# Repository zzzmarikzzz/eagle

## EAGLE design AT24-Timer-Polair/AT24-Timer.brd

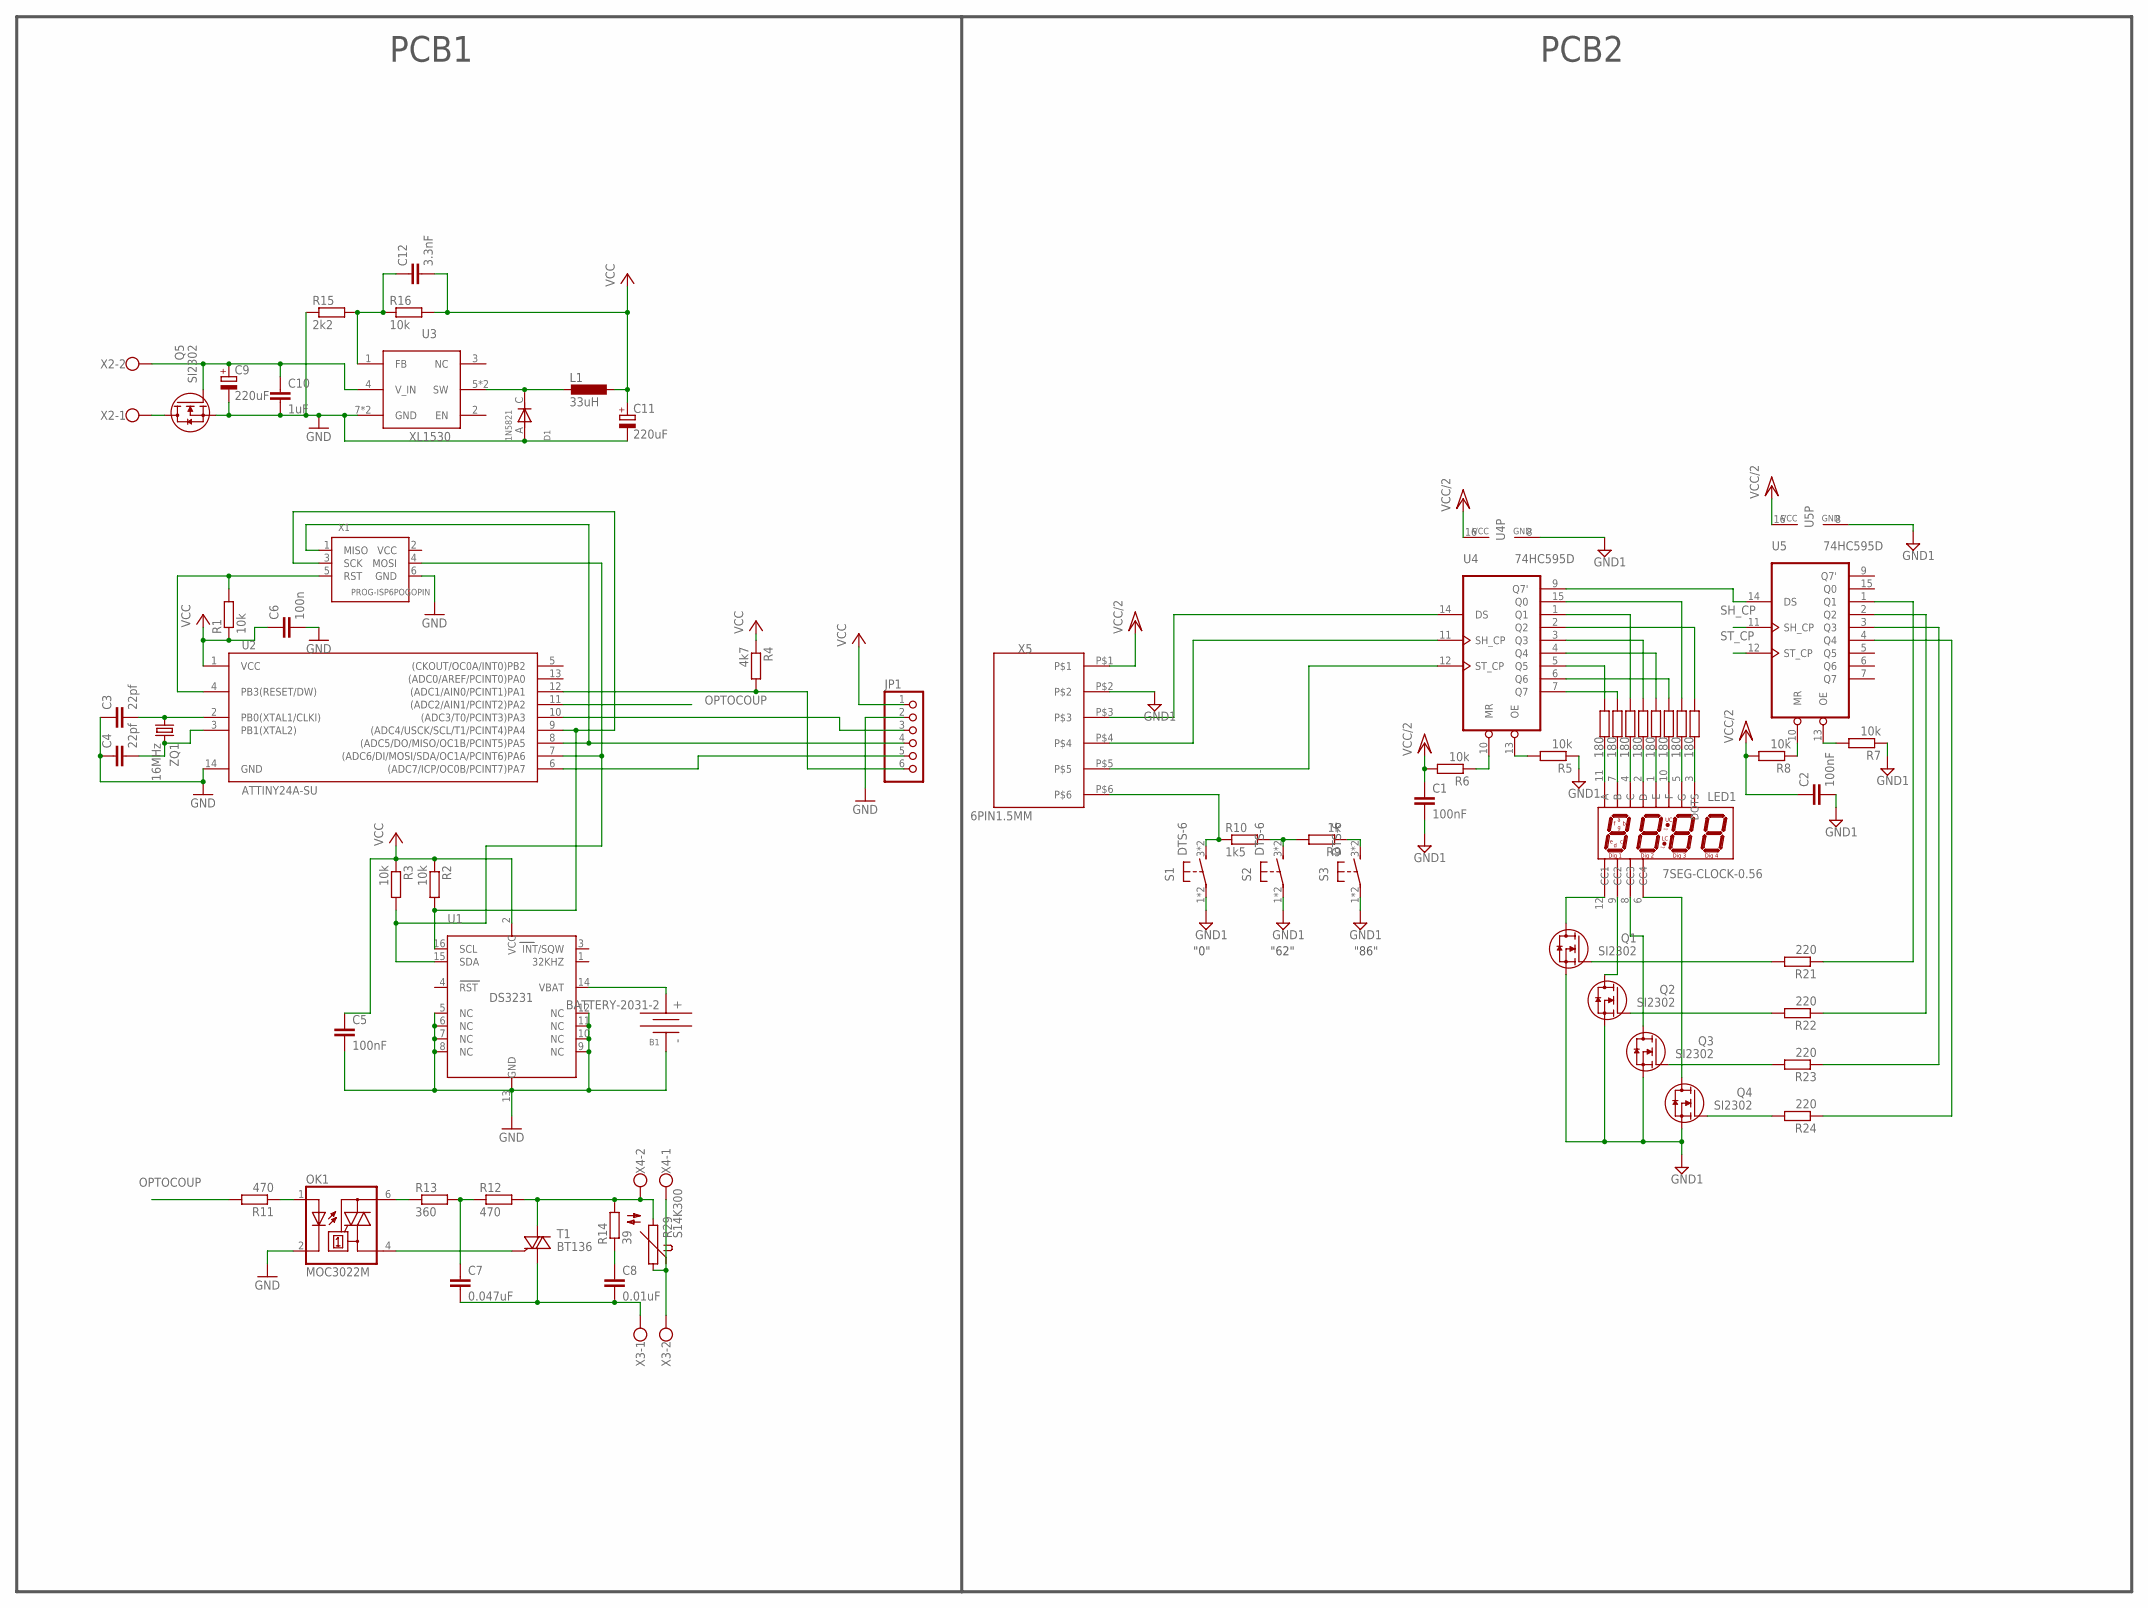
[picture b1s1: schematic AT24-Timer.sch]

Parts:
B1: BATTERY-2031-2; BTH2032-2
C1, C2, C5: 100nF; C0603
C3, C4: 22pf; C0603
C6: 100n; C0603
C7: 0.047uF; C150-054X183
C8: 0.01uF; C102-043X133
C9, C11: 220uF; E2,5-6E
C10: 1uF; C0805
C12: 3.3nF; C0805
D1: 1N5821; DO214AC
JP1: PINHD-1X6; 1X06
L1: 33uH; L-SMD-D10
LED1: 7SEG-CLOCK-0.56; 7SEG_4DIG_0.56
OK1: MOC3022M; DIL06
Q1, Q2, Q3, Q4, Q5: SI2302; SOT-23-GSD
R1, R2, R3, R5, R6, R7, R8: 10k; R0805
R4: 4k7; R0805
R9: 1k; R0805
R10: 1k5; R0805
R11: 470; R0805
R12: 470; 0207/7
R13: 360; 0207/7
R14: 39; 0207/7
R15: 2k2; R0603
R16: 10k; R0603
R17, R18, R19, R20, R25, R26, R27, R28: 180; R0805
R21, R22, R23, R24: 220; R0805
R29: S14K300
S1, S2, S3: DTS-6
T1: BT136; TO220AB
U1: DS3231; SO16L
U2: ATTINY24A-SU; SO14
U3: XL1530; SOP08
U4, U5: 74HC595D; SO16
X1: PROG-ISP6POGOPIN; PROG_POGOPIN
X2, X3, X4: W237-102
X5: 6PIN1.5MM; 6PIN*1.5MM
ZQ1: 16MHz; HC49/S

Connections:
GND: B1.-, C3.1, C4.1, C5.2, C6.2, C9.-, C10.2, C11.-, D1.A (ANOD), JP1.2, OK1.2 (C), Q5.S, R15.1, U1.5 (NC), U1.6 (NC), U1.7 (NC), U1.8 (NC), U1.9 (NC), U1.10 (NC), U1.11 (NC), U1.12 (NC), U1.13 (GND), U2.14 (GND), U3.7 (GND), U3.8 (GND), X1.6 (GND)
GND1: C1.2, C2.2, Q1.S, Q2.S, Q3.S, Q4.S, R5.1, R7.1, S1.1, S1.2 (1), S2.1, S2.2 (1), S3.1, S3.2 (1), U4.8 (GND), U5.8 (GND), X5.P$2
unnamed: R29.1, X3.2, X4.1
unnamed: Q5.D, X2.1
unnamed: R3.2, U1.15 (SDA), U2.7 ((ADC6/DI/MOSI/SDA/OC1A/PCINT6)PA6), X1.4 (MOSI)
unnamed: R2.2, U1.16 (SCL), U2.9 ((ADC4/USCK/SCL/T1/PCINT4)PA4), X1.3 (SCK)
unnamed: R1.2, U2.4 (PB3(RESET/DW)), X1.5 (RST)
unnamed: R10.1, S1.3 (2), S1.4 (2), X5.P$6
unnamed: C3.2, U2.2 (PB0(XTAL1/CLKI)), ZQ1.1
unnamed: C4.2, U2.3 (PB1(XTAL2)), ZQ1.2
unnamed: R6.1, U4.10 (MR)
unnamed: JP1.6, R4.2, U2.12 ((ADC1/AIN0/PCINT1)PA1)
unnamed: U4.14 (DS), X5.P$3
unnamed: C8.1, R14.1
unnamed: C7.2, C8.2, T1.1 (A1), X3.1
unnamed: R12.2, R14.2, R29.2, T1.2 (A2), X4.2
unnamed: R9.1, S3.3 (2), S3.4 (2)
unnamed: OK1.4 (A1), T1.3 (G)
unnamed: C7.1, R12.1, R13.2
unnamed: OK1.6 (A2), R13.1
unnamed: R5.2, U4.13 (OE)
unnamed: OK1.1 (A), R11.1
unnamed: R8.1, U5.10 (MR)
unnamed: JP1.5, U2.6 ((ADC7/ICP/OC0B/PCINT7)PA7)
unnamed: JP1.4, U2.8 ((ADC5/DO/MISO/OC1B/PCINT5)PA5), X1.1 (MISO)
unnamed: R7.2, U5.13 (OE)
unnamed: JP1.3, U2.10 ((ADC3/T0/PCINT3)PA3)
unnamed: R17.1, U4.5 (Q5)
unnamed: R18.1, U4.7 (Q7)
unnamed: U4.9 (Q7'), U5.14 (DS)
unnamed: R19.1, U4.1 (Q1)
unnamed: R20.1, U4.3 (Q3)
unnamed: R25.1, U4.4 (Q4)
unnamed: R26.1, U4.6 (Q6)
unnamed: R27.1, U4.15 (Q0)
unnamed: R28.1, U4.2 (Q2)
unnamed: LED1.12 (CC1), Q1.D
unnamed: LED1.9 (CC2), Q2.D
unnamed: LED1.8 (CC3), Q3.D
unnamed: LED1.6 (CC4), Q4.D
unnamed: R21.1, U5.1 (Q1)
unnamed: R22.1, U5.2 (Q2)
unnamed: R23.1, U5.3 (Q3)
unnamed: R24.1, U5.4 (Q4)
unnamed: C9.+, C10.1, Q5.G, U3.4 (V_IN), X2.2
unnamed: LED1.11 (A), R17.2
unnamed: LED1.7 (B), R18.2
unnamed: C12.1, R15.2, R16.1, U3.1 (FB)
unnamed: D1.C (KATOD), L1.P$2 (2), U3.5 (SW), U3.6 (SW)
unnamed: LED1.4 (C), R19.2
unnamed: B1.+, U1.14 (VBAT)
unnamed: LED1.2 (D), R20.2
unnamed: LED1.1 (E), R25.2
unnamed: LED1.10 (F), R26.2
unnamed: LED1.5 (G), R27.2
unnamed: LED1.3 (DOTS), R28.2
unnamed: Q4.G, R24.2
unnamed: Q3.G, R23.2
unnamed: Q2.G, R22.2
unnamed: Q1.G, R21.2
unnamed: R9.2, R10.2, S2.3 (2), S2.4 (2)
OPTOCOUP: R11.2, U2.11 ((ADC2/AIN1/PCINT2)PA2)
SH_CP: U4.11 (SH_CP), U5.11 (SH_CP), X5.P$4
ST_CP: U4.12 (ST_CP), U5.12 (ST_CP), X5.P$5
VCC: C5.1, C6.1, C11.+, C12.2, JP1.1, L1.P$1 (1), R1.1, R2.1, R3.1, R4.1, R16.2, U1.2 (VCC), U2.1 (VCC)
VCC/2: C1.1, C2.1, R6.2, R8.2, U4.16 (VCC), U5.16 (VCC), X5.P$1

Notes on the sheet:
PCB1
PCB2
"0"
"62"
"86"

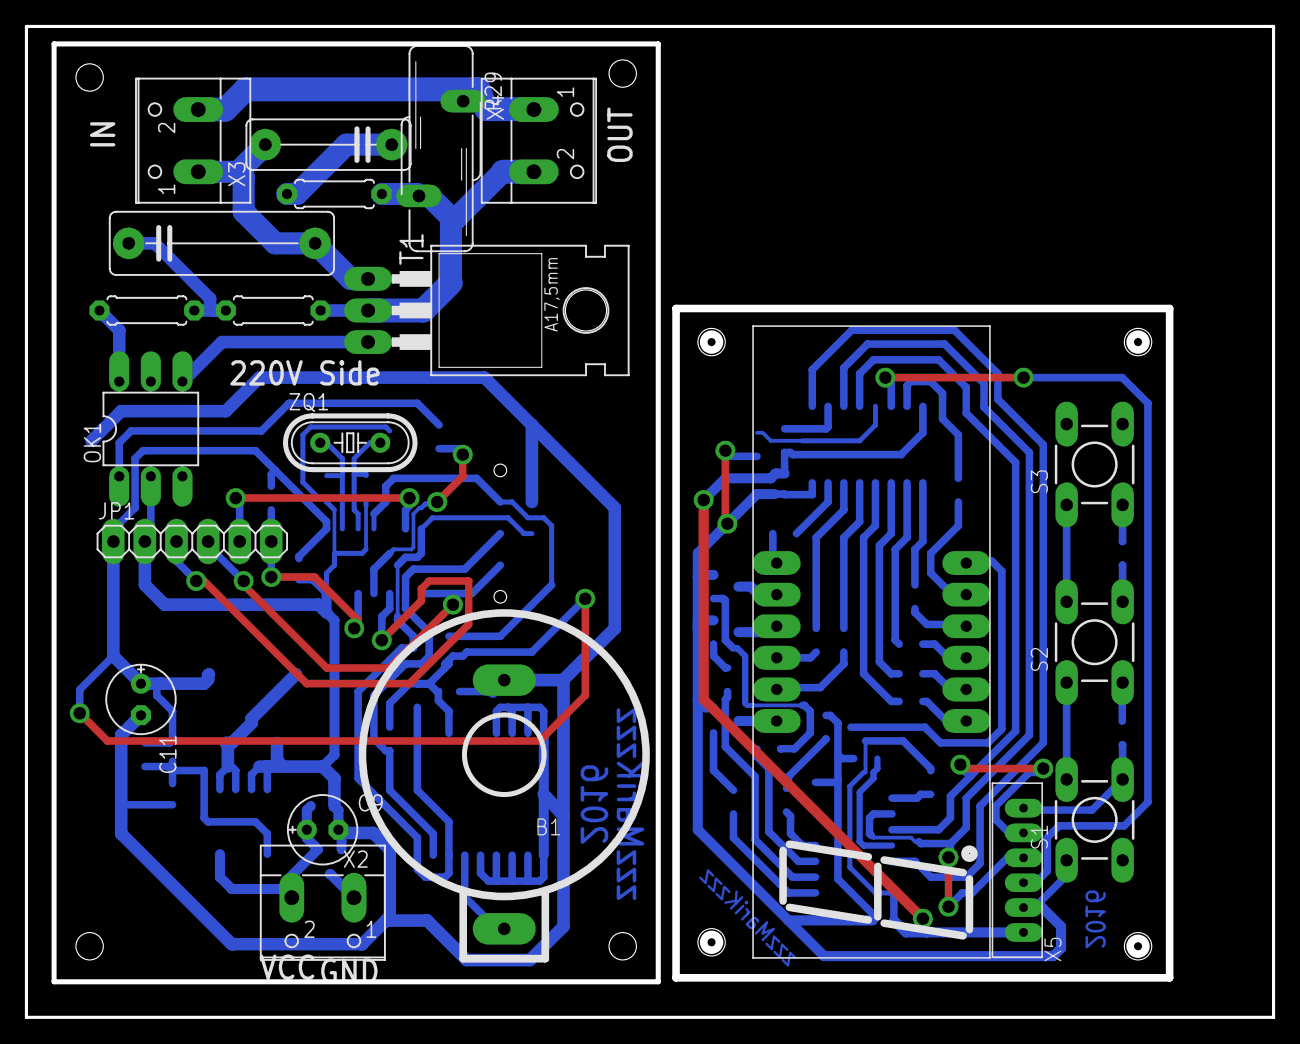
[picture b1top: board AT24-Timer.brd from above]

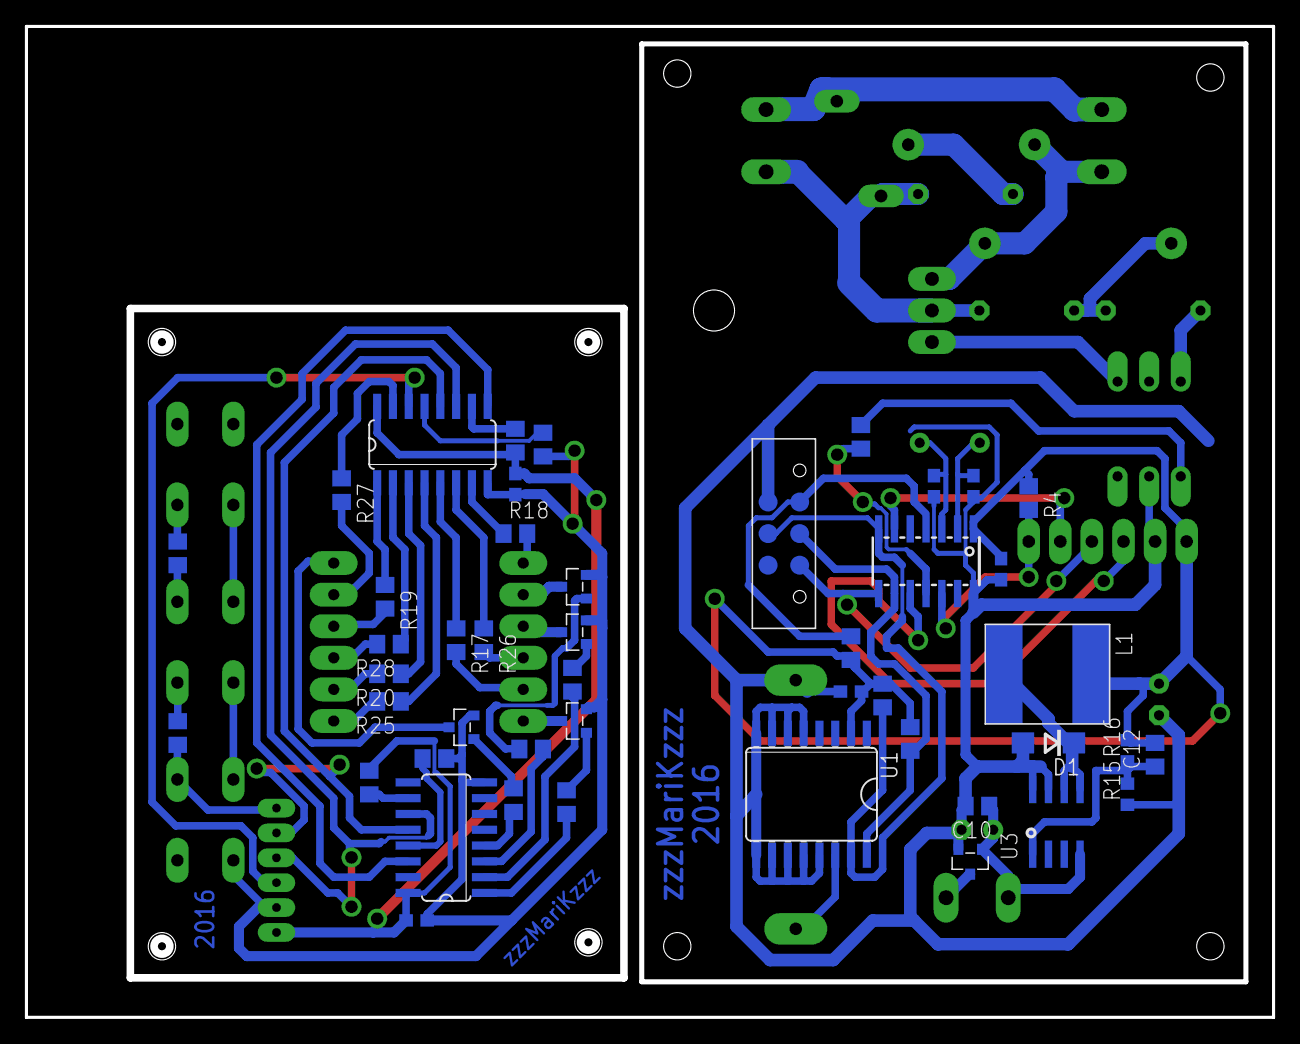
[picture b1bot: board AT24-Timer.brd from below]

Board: 2 copper layers, 100.3 x 79.7 mm, 67 parts (46 on the bottom side), 66 nets.

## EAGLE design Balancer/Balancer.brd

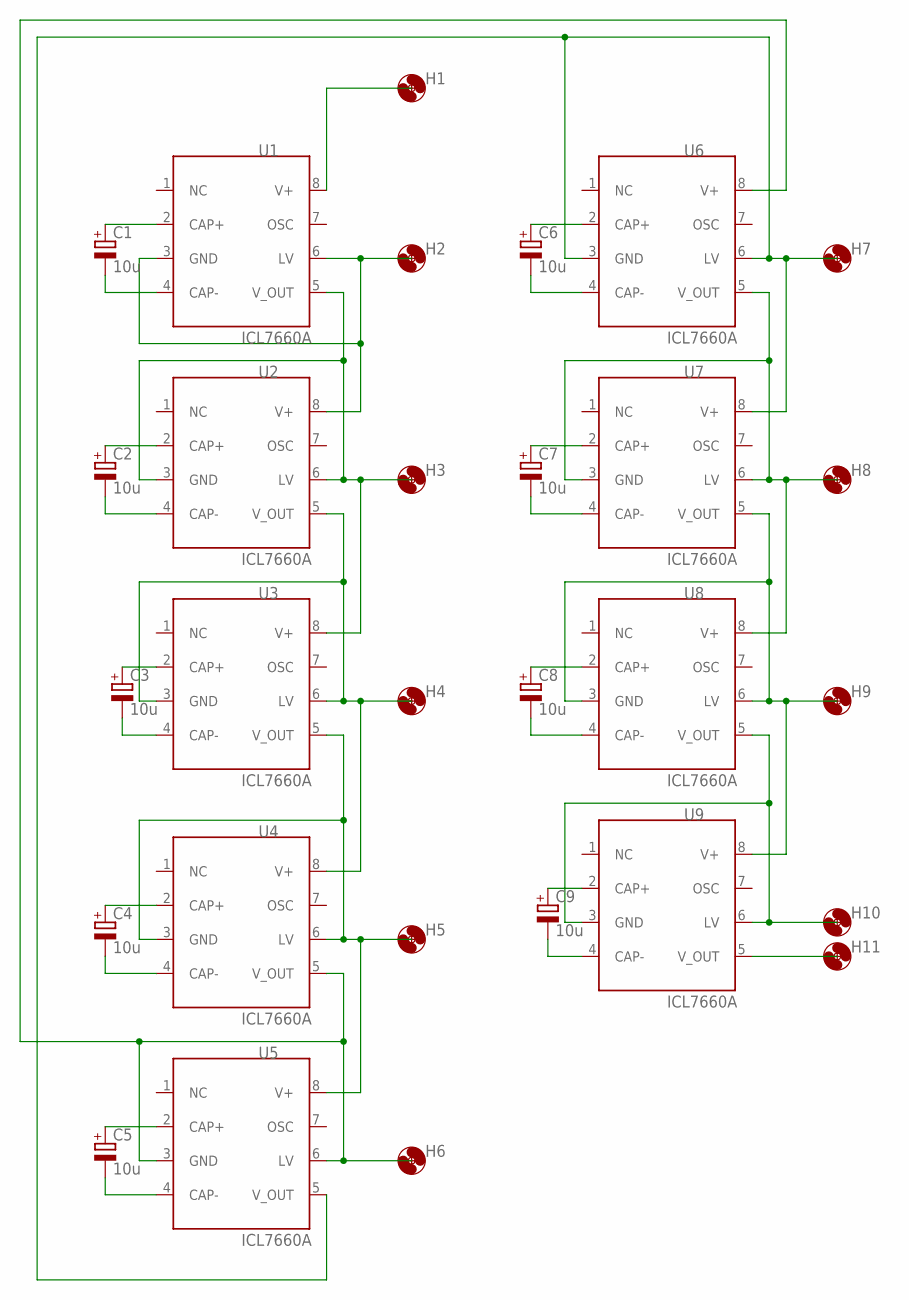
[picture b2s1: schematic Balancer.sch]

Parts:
C1, C2, C3, C4, C5, C6, C7, C8, C9: 10u; CT3216
H1, H2, H3, H4, H5, H6, H7, H8, H9, H10, H11: MOUNT-HOLE3.0; 3,0
U1, U2, U3, U4, U5, U6, U7, U8, U9: ICL7660A; SO08

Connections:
unnamed: C1.+, U1.2 (CAP+)
unnamed: C1.-, U1.4 (CAP-)
unnamed: C2.+, U2.2 (CAP+)
unnamed: C2.-, U2.4 (CAP-)
unnamed: C3.+, U3.2 (CAP+)
unnamed: C3.-, U3.4 (CAP-)
unnamed: C4.+, U4.2 (CAP+)
unnamed: C4.-, U4.4 (CAP-)
unnamed: C5.+, U5.2 (CAP+)
unnamed: C5.-, U5.4 (CAP-)
unnamed: C6.+, U6.2 (CAP+)
unnamed: C6.-, U6.4 (CAP-)
unnamed: C7.+, U7.2 (CAP+)
unnamed: C7.-, U7.4 (CAP-)
unnamed: C8.+, U8.2 (CAP+)
unnamed: C8.-, U8.4 (CAP-)
unnamed: C9.+, U9.2 (CAP+)
unnamed: C9.-, U9.4 (CAP-)
unnamed: H1.P$1, U1.8 (V+)
unnamed: H2.P$1, U1.3 (GND), U1.6 (LV), U2.8 (V+)
unnamed: H3.P$1, U1.5 (V_OUT), U2.3 (GND), U2.6 (LV), U3.8 (V+)
unnamed: H4.P$1, U2.5 (V_OUT), U3.3 (GND), U3.6 (LV), U4.8 (V+)
unnamed: H5.P$1, U3.5 (V_OUT), U4.3 (GND), U4.6 (LV), U5.8 (V+)
unnamed: H6.P$1, U4.5 (V_OUT), U5.3 (GND), U5.6 (LV), U6.8 (V+)
unnamed: H7.P$1, U5.5 (V_OUT), U6.3 (GND), U6.6 (LV), U7.8 (V+)
unnamed: H8.P$1, U6.5 (V_OUT), U7.3 (GND), U7.6 (LV), U8.8 (V+)
unnamed: H9.P$1, U7.5 (V_OUT), U8.3 (GND), U8.6 (LV), U9.8 (V+)
unnamed: H10.P$1, U8.5 (V_OUT), U9.3 (GND), U9.6 (LV)
unnamed: H11.P$1, U9.5 (V_OUT)

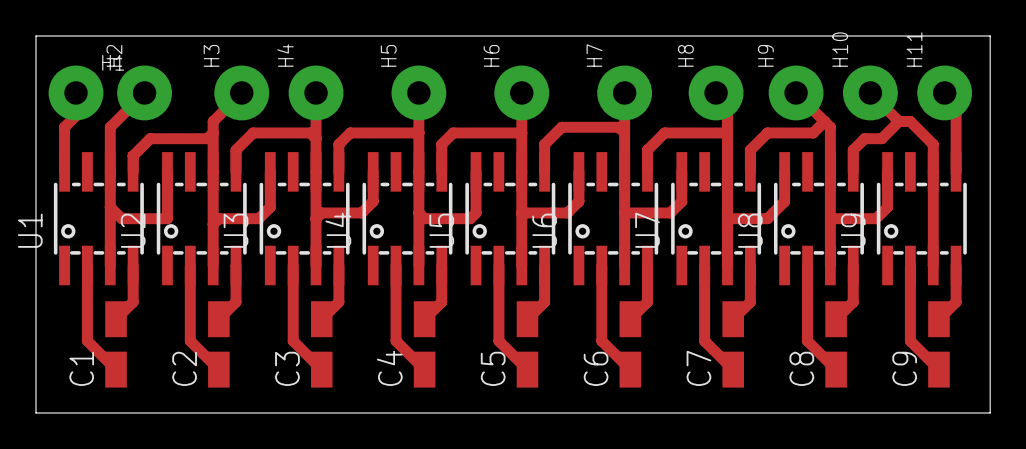
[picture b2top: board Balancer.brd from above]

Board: 2 copper layers, 53.0 x 20.9 mm, 29 parts (0 on the bottom side), 29 nets.

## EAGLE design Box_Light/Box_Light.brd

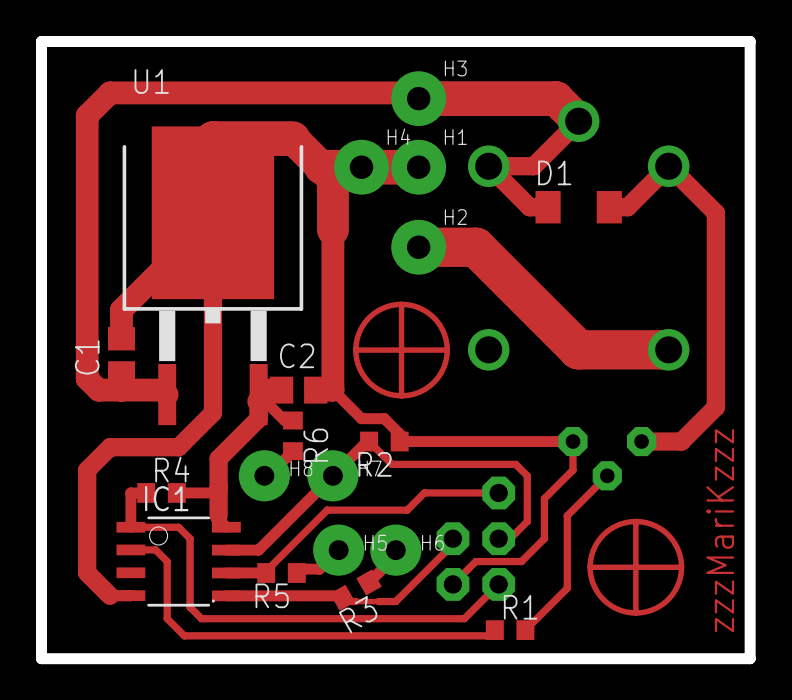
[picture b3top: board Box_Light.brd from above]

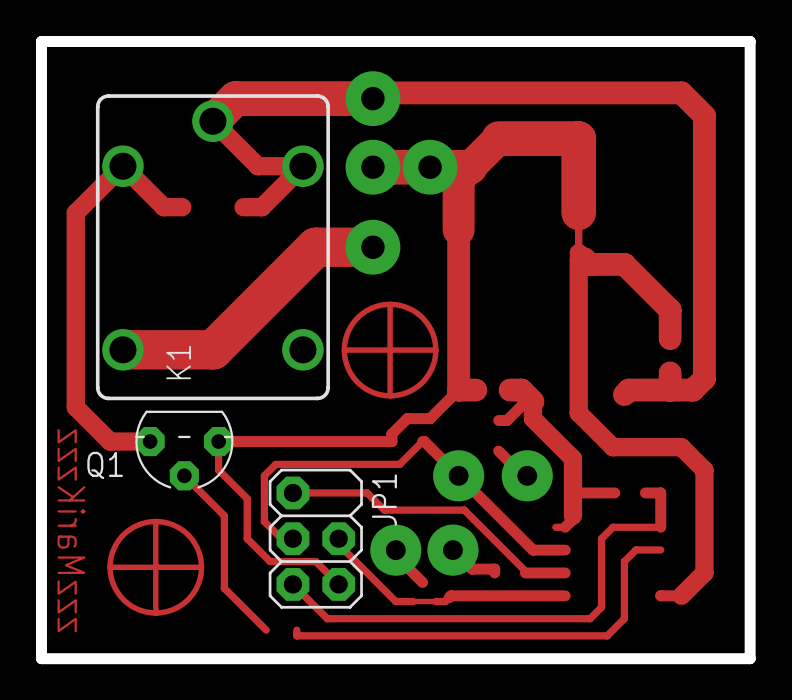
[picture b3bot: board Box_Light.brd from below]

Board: 2 copper layers, 39.4 x 34.3 mm, 22 parts (3 on the bottom side), 14 nets.

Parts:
C1: 330nf; C0805
C2: 100nf; C0805
D1: DIODE; SOD80
H1: Light -; 3,0
H2: Light +; 3,0
H3: +12V; 3,0
H4: GND; 3,0
H5: Door 2; 2,8
H6: Door 1; 2,8
H7: Key-; 2,8
H8: Key+; 2,8
IC1: TINY13-20SSU; 8S1
JP1: 2X2.5
K1: CQ1-12V; CQ1
Q1: S9014; TO92
R1, R3, R4, R5: 10k; R0603
R2: 68k; R0603
R6: 6k8; R0603
U1: L7805; TO263

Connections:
+5V: C2.1, IC1.8, R4.2, R6.1, U1.2
+12V: C1.1, D1.1, H3.P$1, K1.1, K1.C, U1.1
GND: C1.2, C2.2, H1.P$1, H4.P$1, IC1.4, JP1.6, Q1.3, R2.1, U1.3
unnamed: D1.2, K1.2, Q1.1
unnamed: Q1.2, R1.2
unnamed: H7.P$1, IC1.7, JP1.3, R2.2
unnamed: H5.P$1, R5.1
unnamed: IC1.5, JP1.4, R3.2
unnamed: IC1.2, R1.1
unnamed: IC1.6, JP1.1, R5.2
unnamed: IC1.1, JP1.5, R4.1
unnamed: H2.P$1, K1.NO
unnamed: H6.P$1, R3.1
unnamed: H8.P$1, R6.2

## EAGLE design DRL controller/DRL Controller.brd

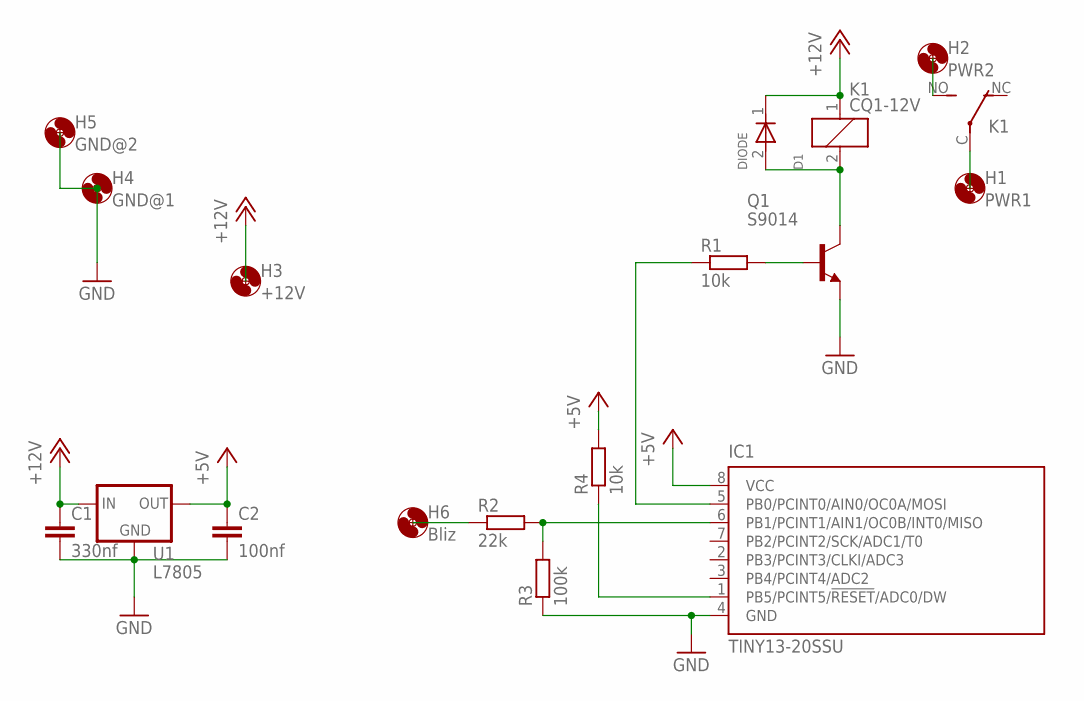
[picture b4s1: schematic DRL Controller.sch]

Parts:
C1: 330nf; C0805
C2: 100nf; C0805
D1: DIODE; SOD80
H1: PWR1; 3,0
H2: PWR2; 3,0
H3: +12V; 2,8
H4: GND@1; 2,8
H5: GND@2; 3,0
H6: Bliz; 2,8
IC1: TINY13-20SSU; 8S1
K1: CQ1-12V; CQ1
Q1: S9014; TO92
R1, R4: 10k; R0805
R2: 22k; R0805
R3: 100k; R0805
U1: L7805; TO263

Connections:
+5V: C2.1, IC1.8 (VCC), R4.2, U1.2 (OUT)
+12V: C1.1, D1.1 (KATOD), H3.P$1, K1.1, U1.1 (IN)
GND: C1.2, C2.2, H4.P$1, H5.P$1, IC1.4 (GND), Q1.3 (E), R3.1, U1.3 (GND)
unnamed: D1.2 (ANOD), K1.2, Q1.1 (C)
unnamed: Q1.2 (B), R1.2
unnamed: H1.P$1, K1.C
unnamed: H2.P$1, K1.NO (S)
unnamed: IC1.6 (PB1/PCINT1/AIN1/OC0B/INT0/MISO), R2.2, R3.2
unnamed: IC1.5 (PB0/PCINT0/AIN0/OC0A/MOSI), R1.1
unnamed: H6.P$1, R2.1
unnamed: IC1.1 (PB5/PCINT5/!RESET!/ADC0/DW), R4.1

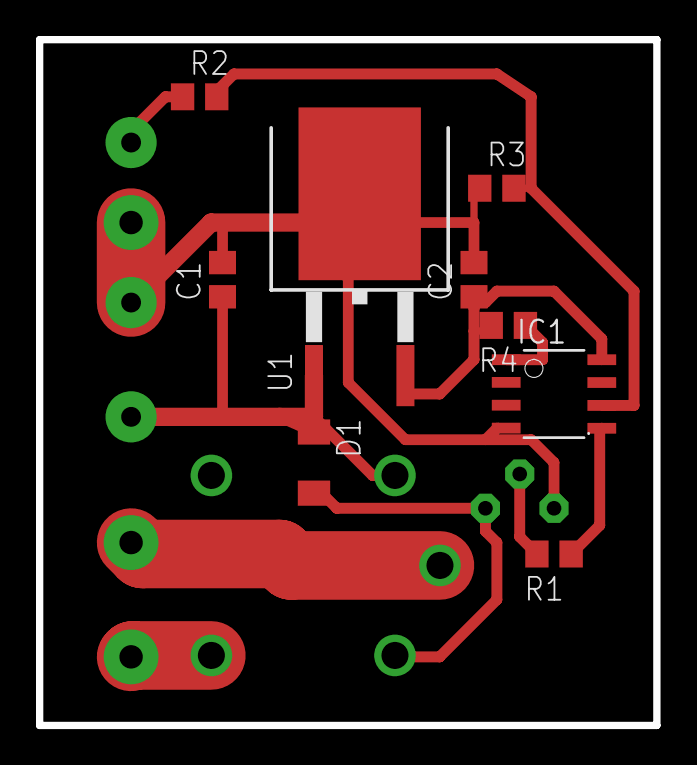
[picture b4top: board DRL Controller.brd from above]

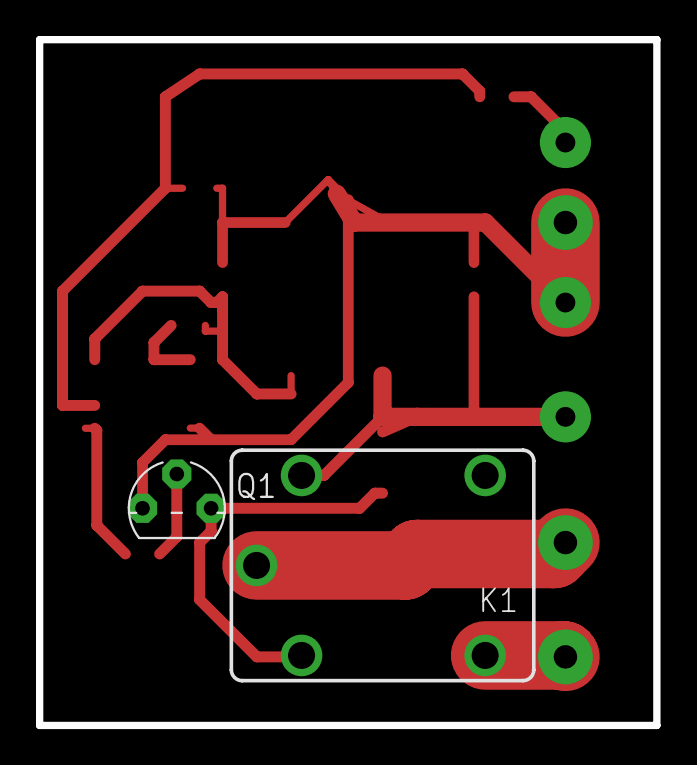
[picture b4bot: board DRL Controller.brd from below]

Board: 2 copper layers, 34.3 x 38.1 mm, 17 parts (2 on the bottom side), 11 nets.
